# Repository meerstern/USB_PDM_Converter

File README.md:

# USB_PDM_Converter
USB-PDM Converter with CS53L30 &amp; CP2615

## 概要 
  * [USB オーディオブリッジIC CP2615][1]と[ADコンバータ CS53L30][2]を使用したUSB-PDM変換基板です  
  * 2個のデジタルPDM出力MEMSマイクをUSBオーディオデバイス(ステレオ)に変換します  
  * 24bit、44.1kHz/48kHzサンプリングで変換します  
  * デジタルPDM出力MEMSマイクの評価や動作確認に便利です  
  * デジタルPDM出力MEMSマイク電源は既定値で2.75Vです 
  * デジタルPDM出力MEMSマイククロックは既定値で3MHzです 
  * 2個のPDM出力MEMSマイクをUSBオーディオデバイスとして認識するためのパラメータを予め書き込んでおります  
  * OS標準のUSBオーディオデバイスとして認識されるため、ドライバは不要です  
  * [Simplicity Studio][3]を用いたCP2615のパラメータ書き換え例(デジタルMIC、アナログMIC)を用意しています  
  * [デジタル出力MEMSマイク変換基板][4]を2つ接続可能です  
  * デジタルPDM出力MEMSマイク1つの場合はモノラル出力として利用可能です  
  * サイズ40mm x50mm、M3穴x2、間隔34mm  

## 注意
  * PDM出力マイクは付属しておりませんので別途ご用意ください  
  * CS53L30の設定を変更する場合はCP2615のパラメータ変更が必要です  
  * 本変換基板とPDM出力マイクとの接続ケーブルはノイズ低減のため、30mm程度以下にしてください  
  * CP2615のパラメータを変更する場合は[Simplicity Studio][3]が必要です  
  * CP2615のパラメータを変更する場合はPIDを0xEA93に変更したCP2112が必要です  
  * CS53L30は4つのマイクを接続可能ですが、CP2615の制約で同時接続できるマイクは最大2つです  
  * MIC2側を使用する場合はR3をRX1に置き換えてください  
  * アナログMEMSマイクを使用する場合はCP2615のパラメータ書き換えが必要です  
  * CP2615はFlashベースのため、パラメータ変更の回数制約はありません  
 
## 販売サイト
  * [スイッチサイエンス][5]

## 告知
  * CP2615は生産完了予定品となっています 新規開発用途には向いていません  
  * 21年8月から22年4月頃販売の製品の一部に誤ったパラメータが書き込まれた製品があることが判明しました  
  * 購入後、マイクとして動作しない等が見られた場合はお手数ですがCrescentまでお問い合わせください  

[1]: https://jp.silabs.com/interface/usb-audio-bridges/device.cp2615
[2]: https://www.cirrus.com/products/cs53l30/
[3]: https://jp.silabs.com/products/development-tools/software/simplicity-studio
[4]: https://www.switch-science.com/catalog/3379/
[5]: https://www.switch-science.com/products/6488

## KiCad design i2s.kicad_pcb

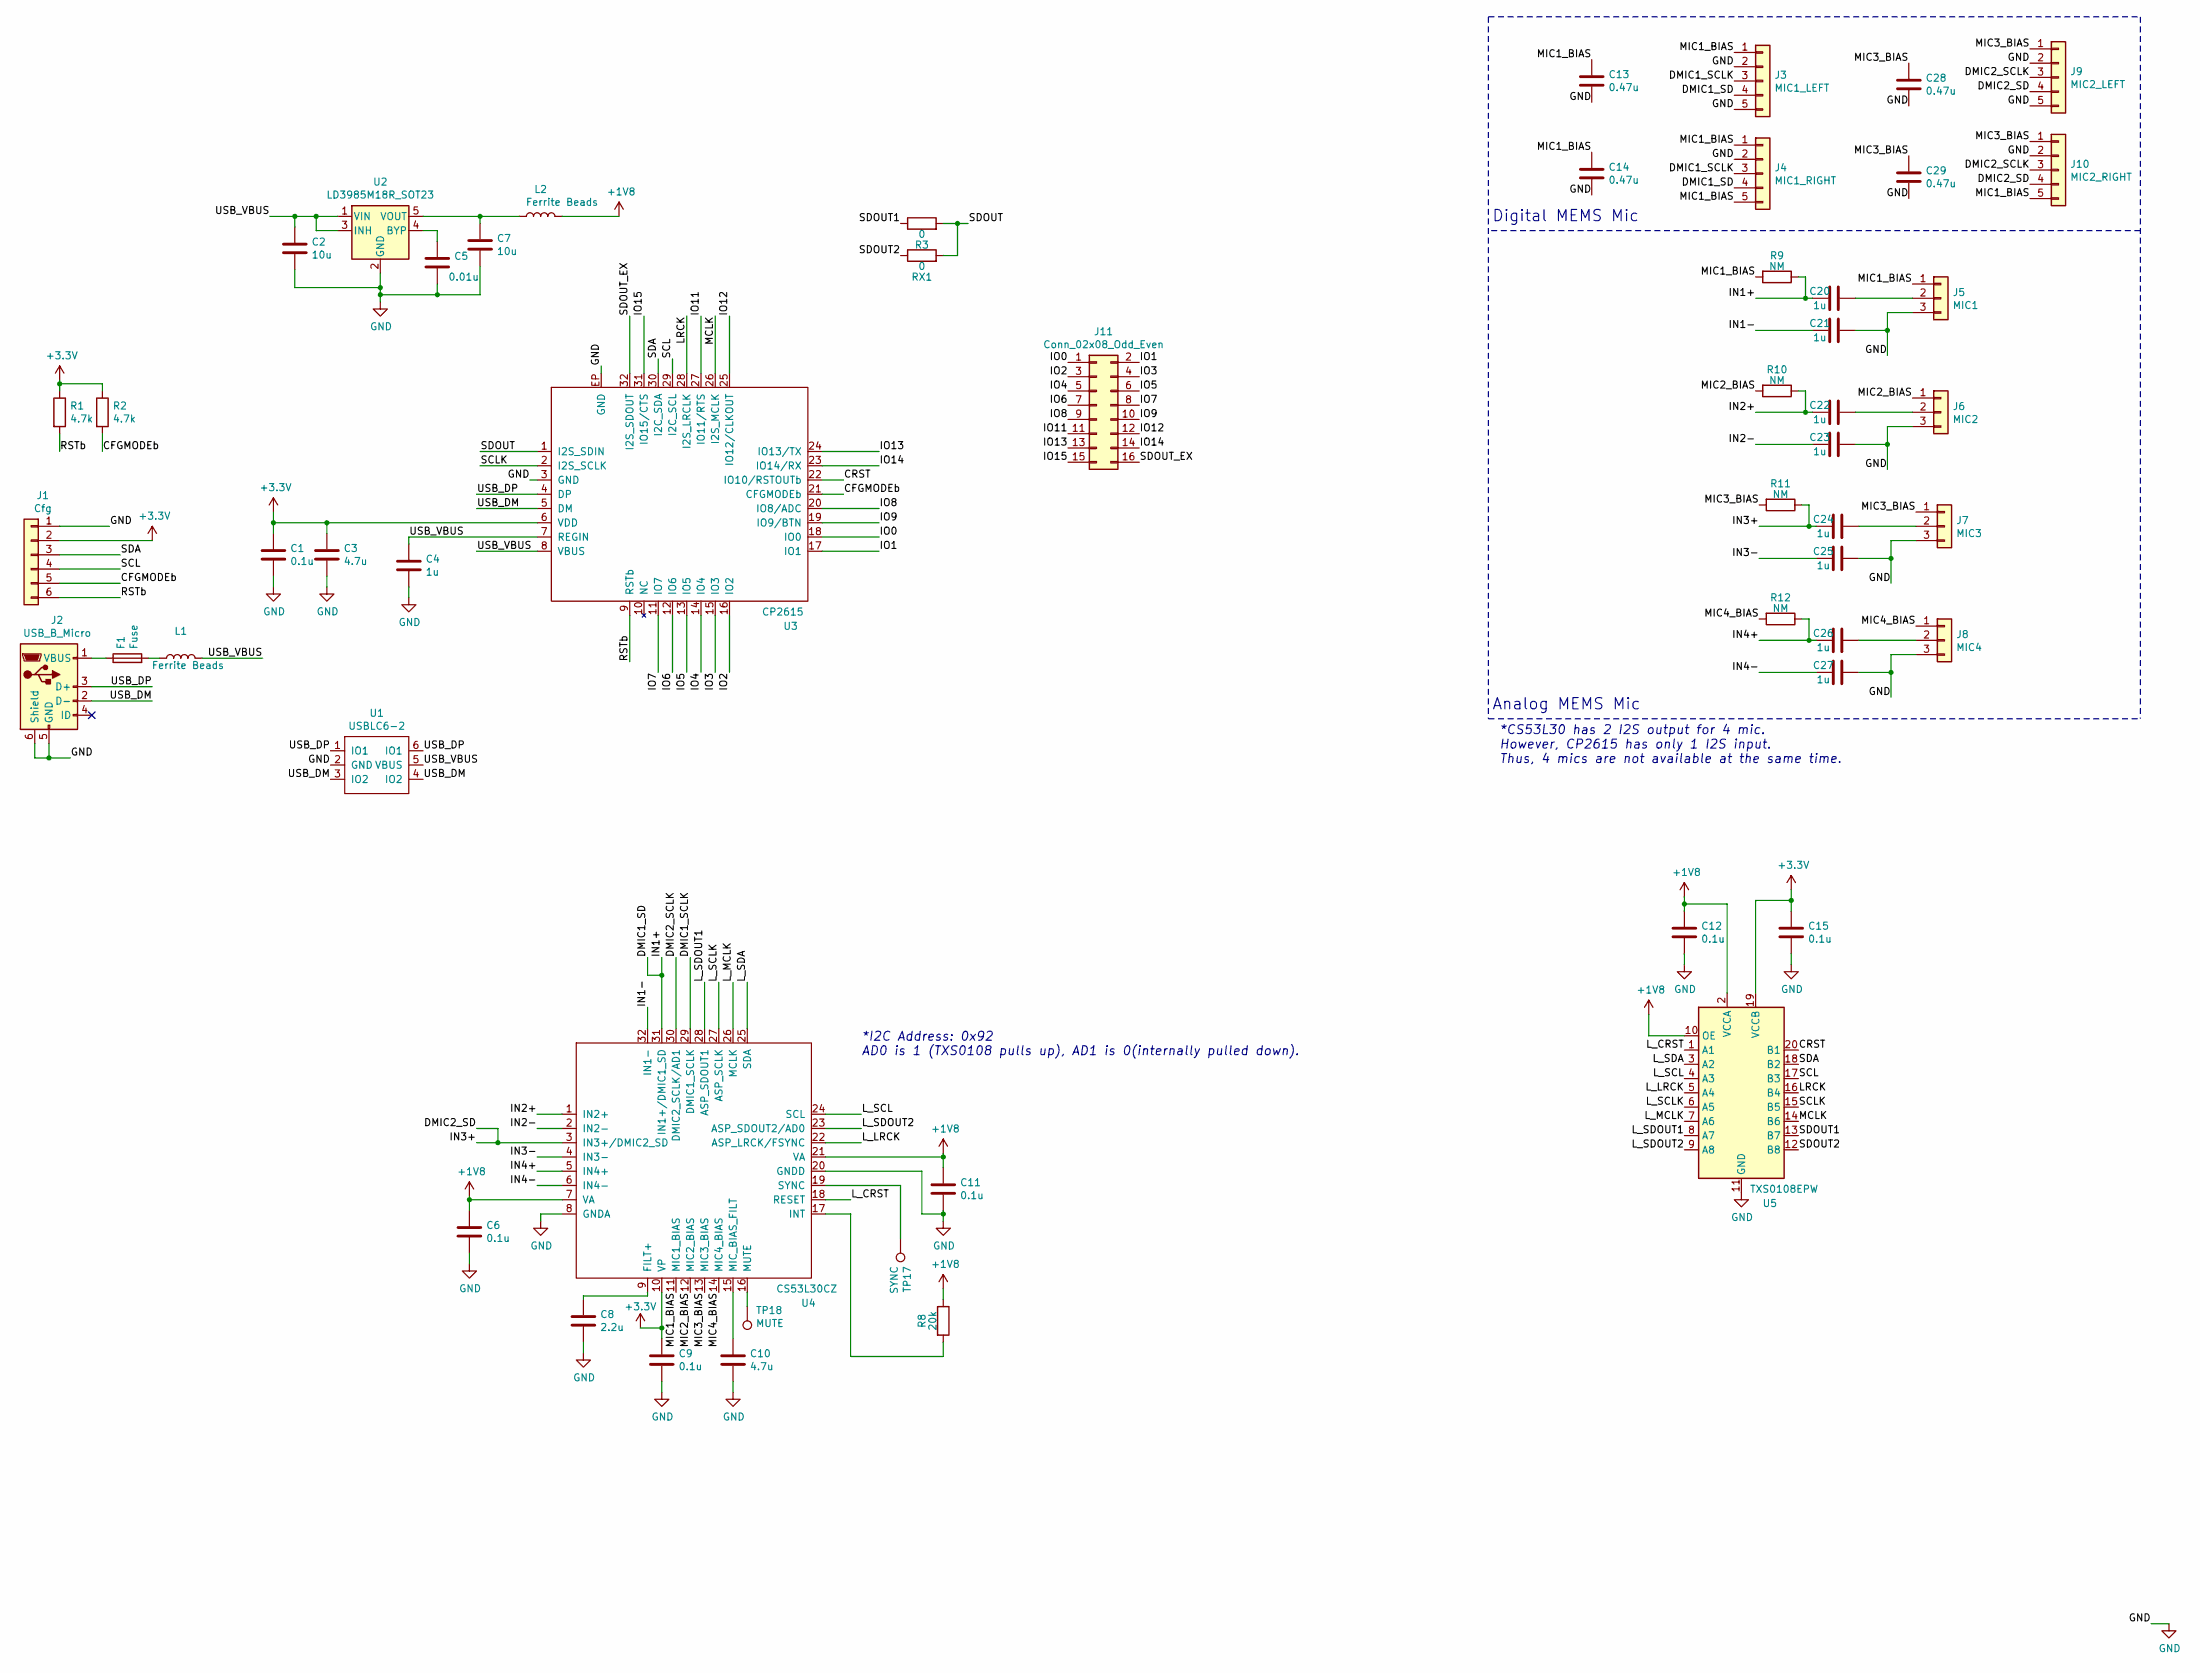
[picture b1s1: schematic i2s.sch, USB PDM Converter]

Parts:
C1, C6, C9, C11, C12, C15: 0.1u; C_0603_1608Metric
C2, C7: 10u; C_0805_2012Metric
C3, C10: 4.7u; C_0805_2012Metric
C4, C20, C21, C22, C23, C24, C25, C26, C27: 1u; C_0603_1608Metric
C5: 0.01u; C_0603_1608Metric
C8: 2.2u; C_0603_1608Metric
C13, C14, C28, C29: 0.47u; C_0603_1608Metric
F1: Fuse; Fuse_0603_1608Metric
J1: Cfg; PinHeader_1x06_P2.54mm_Vertical
J2: USB_B_Micro; CONN-10118194-0001LF-FCI
J3: MIC1_LEFT; PinHeader_1x05_P2.54mm_Vertical
J4: MIC1_RIGHT; PinHeader_1x05_P2.54mm_Vertical
J5: MIC1; PinHeader_1x03_P2.54mm_Vertical
J6: MIC2; PinHeader_1x03_P2.54mm_Vertical
J7: MIC3; PinHeader_1x03_P2.54mm_Vertical
J8: MIC4; PinHeader_1x03_P2.54mm_Vertical
J9: MIC2_LEFT; PinHeader_1x05_P2.54mm_Vertical
J10: MIC2_RIGHT; PinHeader_1x05_P2.54mm_Vertical
J11: Conn_02x08_Odd_Even; PinHeader_2x08_P1.27mm_Vertical
L1, L2: Ferrite Beads; L_0603_1608Metric
R1, R2: 4.7k; R_0603_1608Metric
R3: 0; R_0603_1608Metric
R8: 20k; R_0603_1608Metric
R9, R10, R11, R12: NM; R_0603_1608Metric
RX1: 0; R_0603_1608Metric
TP17: SYNC; TestPoint_Pad_D1.0mm
TP18: MUTE; TestPoint_Pad_D1.0mm
U1: USBLC6-2; SOT-23-6
U2: LD3985M18R_SOT23; SOT-23-5
U3: CP2615; QFN-32-1EP_5x5mm_P0.5mm_EP3.1x3.1mm
U4: CS53L30CZ; QFN-32-1EP_5x5mm_P0.5mm_EP3.1x3.1mm
U5: TXS0108EPW; TSSOP-20_4.4x6.5mm_P0.65mm

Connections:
+1V8: C6.1, C11.1, C12.1, L2.2, R8.1, U4.7 (VA), U4.21 (VA), U5.2 (VCCA), U5.10 (OE)
+3V3: C1.1, C3.1, C9.1, C15.1, J1.2, R1.1, R2.1, U3.6 (VDD), U4.10 (VP), U5.19 (VCCB)
/CFGMODEb: J1.5, R2.2, U3.21 (CFGMODEb)
/CRST: U3.22 (IO10/RSTOUTb), U5.20 (B1)
/DMIC1_SCLK: J3.3, J4.3, U4.29 (DMIC1_SCLK)
/DMIC1_SD: C20.2, J3.4, J4.4, R9.1, U4.31 (IN1+/DMIC1_SD)
/DMIC2_SCLK: J9.3, J10.3, U4.30 (DMIC2_SCLK/AD1)
/DMIC2_SD: C24.2, J9.4, J10.4, R11.1, U4.3 (IN3+/DMIC2_SD)
/IN1-: C21.2, U4.32 (IN1-)
/IN2+: C22.2, R10.1, U4.1 (IN2+)
/IN2-: C23.2, U4.2 (IN2-)
/IN3-: C25.2, U4.4 (IN3-)
/IN4+: C26.2, R12.1, U4.5 (IN4+)
/IN4-: C27.2, U4.6 (IN4-)
/IO0: J11.1, U3.18 (IO0)
/IO1: J11.2, U3.17 (IO1)
/IO2: J11.3, U3.16 (IO2)
/IO3: J11.4, U3.15 (IO3)
/IO4: J11.5, U3.14 (IO4)
/IO5: J11.6, U3.13 (IO5)
/IO6: J11.7, U3.12 (IO6)
/IO7: J11.8, U3.11 (IO7)
/IO8: J11.9, U3.20 (IO8/ADC)
/IO9: J11.10, U3.19 (IO9/BTN)
/IO11: J11.11, U3.27 (IO11/RTS)
/IO12: J11.12, U3.25 (IO12/CLKOUT)
/IO13: J11.13, U3.24 (IO13/TX)
/IO14: J11.14, U3.23 (IO14/RX)
/IO15: J11.15, U3.31 (IO15/CTS)
/LRCK: U3.28 (I2S_LRCLK), U5.16 (B4)
/L_CRST: U4.18 (RESET), U5.1 (A1)
/L_LRCK: U4.22 (ASP_LRCK/FSYNC), U5.5 (A4)
/L_MCLK: U4.26 (MCLK), U5.7 (A6)
/L_SCL: U4.24 (SCL), U5.4 (A3)
/L_SCLK: U4.27 (ASP_SCLK), U5.6 (A5)
/L_SDA: U4.25 (SDA), U5.3 (A2)
/L_SDOUT1: U4.28 (ASP_SDOUT1), U5.8 (A7)
/L_SDOUT2: U4.23 (ASP_SDOUT2/AD0), U5.9 (A8)
/MCLK: U3.26 (I2S_MCLK), U5.14 (B6)
/MIC1_BIAS: C13.1, C14.1, J3.1, J4.1, J4.5, J5.1, J10.5, R9.2, U4.11 (MIC1_BIAS)
/MIC2_BIAS: J6.1, R10.2, U4.12 (MIC2_BIAS)
/MIC3_BIAS: C28.1, C29.1, J7.1, J9.1, J10.1, R11.2, U4.13 (MIC3_BIAS)
/MIC4_BIAS: J8.1, R12.2, U4.14 (MIC4_BIAS)
/RSTb: J1.6, R1.2, U3.9 (RSTb)
/SCL: J1.4, U3.29 (I2C_SCL), U5.17 (B3)
/SCLK: U3.2 (I2S_SCLK), U5.15 (B5)
/SDA: J1.3, U3.30 (I2C_SDA), U5.18 (B2)
/SDOUT: R3.2, RX1.2, U3.1 (I2S_SDIN)
/SDOUT1: R3.1, U5.13 (B7)
/SDOUT2: RX1.1, U5.12 (B8)
/SDOUT_EX: J11.16, U3.32 (I2S_SDOUT)
/USB_DM: J2.2 (D-), U1.3 (IO2), U1.4 (IO2), U3.5 (DM)
/USB_DP: J2.3 (D+), U1.1 (IO1), U1.6 (IO1), U3.4 (DP)
/USB_VBUS: C2.1, C4.1, L1.2, U1.5 (VBUS), U2.1 (VIN), U2.3 (INH), U3.7 (REGIN), U3.8 (VBUS)
GND: C1.2, C2.2, C3.2, C4.2, C5.2, C6.2, C7.2, C8.2, C9.2, C10.2, C11.2, C12.2, C13.2, C14.2, C15.2, C21.1, C23.1, C25.1, C27.1, C28.2, C29.2, J1.1, J2.5 (GND), J2.6 (Shield), J3.2, J3.5, J4.2, J5.3, J6.3, J7.3, J8.3, J9.2, J9.5, J10.2, U1.2 (GND), U2.2 (GND), U3.3 (GND), U3.33, U3.EP (GND), U4.8 (GNDA), U4.20 (GNDD), U5.11 (GND)
unnamed: C5.1, U2.4 (BYP)
unnamed: C7.1, L2.1, U2.5 (VOUT)
unnamed: C8.1, U4.9 (FILT+)
unnamed: C10.1, U4.15 (MIC_BIAS_FILT)
unnamed: C20.1, J5.2
unnamed: C22.1, J6.2
unnamed: C24.1, J7.2
unnamed: C26.1, J8.2
unnamed: F1.1, J2.1 (VBUS)
unnamed: F1.2, L1.1
unnamed: R8.2, U4.17 (INT)
unnamed: TP17.1, U4.19 (SYNC)
unnamed: TP18.1, U4.16 (MUTE)

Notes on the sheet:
Digital MEMS Mic
Analog MEMS Mic
*CS53L30 has 2 I2S output for 4 mic. However, CP2615 has only 1 I2S input. Thus, 4 mics are not available at the same time.
*I2C Address: 0x92 AD0 is 1 (TXS0108 pulls up), AD1 is 0(internally pulled down).

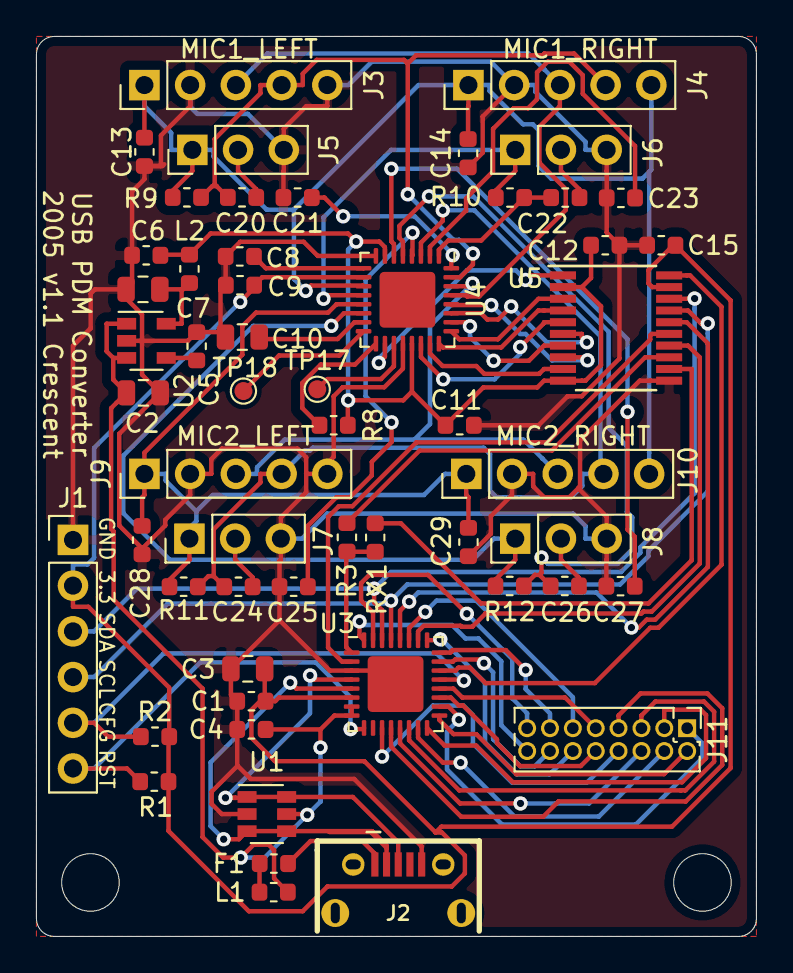
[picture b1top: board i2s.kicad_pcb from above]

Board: 2 copper layers, 40.0 x 50.0 mm, 57 parts (0 on the bottom side), 68 nets.

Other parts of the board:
REF1, REF2: MountingHole_3.2mm_M3

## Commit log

2020-06-07 Add pcb data
2020-06-17 Add README
2020-07-04 Add img files
2020-07-05 Add Pin image
2020-07-05 Simplicity Studio Sample Settings
